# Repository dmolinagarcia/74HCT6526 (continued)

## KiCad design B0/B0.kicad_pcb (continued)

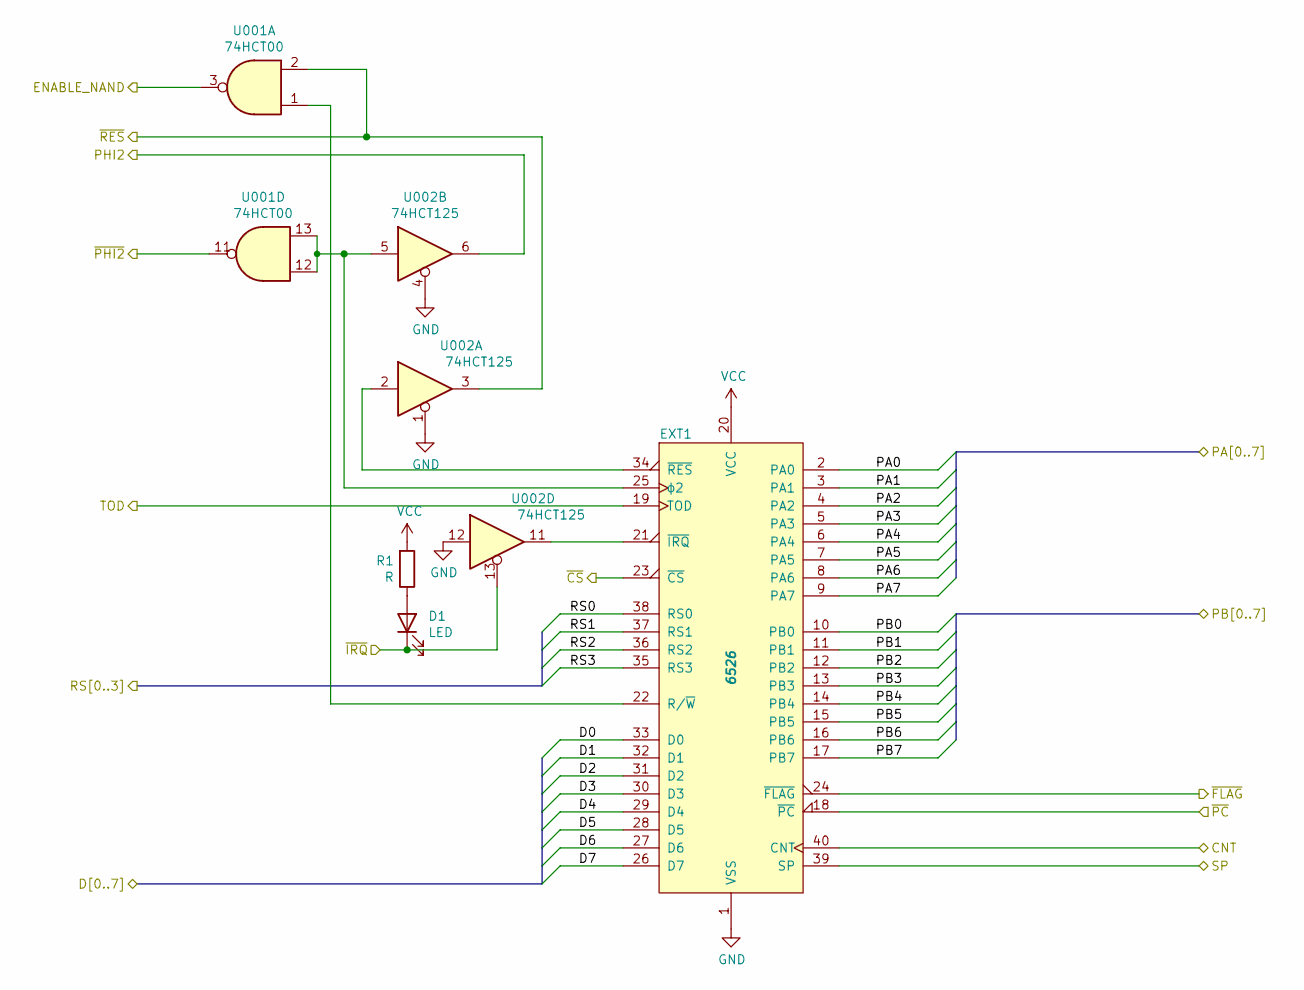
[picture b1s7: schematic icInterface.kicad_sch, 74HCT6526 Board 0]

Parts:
D1: LED; LED_0805_2012Metric
EXT1: 6526; IC Interface 2x20
R1: R; R_0805_2012Metric
U001: 74HCT00; SO-14
U002: 74HCT125; SO-14

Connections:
/icInterface/PA0: EXT1.2 (PA0); also elsewhere on the board
/icInterface/PA1: EXT1.3 (PA1); also elsewhere on the board
/icInterface/PA2: EXT1.4 (PA2); also elsewhere on the board
/icInterface/PA3: EXT1.5 (PA3); also elsewhere on the board
/icInterface/PA4: EXT1.6 (PA4); also elsewhere on the board
/icInterface/PA5: EXT1.7 (PA5); also elsewhere on the board
/icInterface/PA6: EXT1.8 (PA6); also elsewhere on the board
/icInterface/PA7: EXT1.9 (PA7); also elsewhere on the board
/icInterface/PB0: EXT1.10 (PB0); also elsewhere on the board
/icInterface/PB1: EXT1.11 (PB1); also elsewhere on the board
/icInterface/PB2: EXT1.12 (PB2); also elsewhere on the board
/icInterface/PB3: EXT1.13 (PB3); also elsewhere on the board
/icInterface/PB4: EXT1.14 (PB4); also elsewhere on the board
/icInterface/PB5: EXT1.15 (PB5); also elsewhere on the board
/icInterface/PB6: EXT1.16 (PB6); also elsewhere on the board
/icInterface/PB7: EXT1.17 (PB7); also elsewhere on the board
/icInterface/RS0: EXT1.38 (RS0); also elsewhere on the board
/icInterface/RS1: EXT1.37 (RS1); also elsewhere on the board
/icInterface/RS2: EXT1.36 (RS2); also elsewhere on the board
/icInterface/RS3: EXT1.35 (RS3); also elsewhere on the board
/icInterface/~CS: EXT1.23 (~CS); also elsewhere on the board
/icInterface/~PC: EXT1.18 (~PC); also elsewhere on the board
/~PHI2: U001.11; also elsewhere on the board
CNT: EXT1.40 (CNT); also elsewhere on the board
D0: EXT1.33 (D0); also elsewhere on the board
D1: EXT1.32 (D1); also elsewhere on the board
D2: EXT1.31 (D2); also elsewhere on the board
D3: EXT1.30 (D3); also elsewhere on the board
D4: EXT1.29 (D4); also elsewhere on the board
D5: EXT1.28 (D5); also elsewhere on the board
D6: EXT1.27 (D6); also elsewhere on the board
D7: EXT1.26 (D7); also elsewhere on the board
ENABLE_NAND: U001.3; also elsewhere on the board
GND: EXT1.1 (VSS), U002.1, U002.4, U002.12; also elsewhere on the board
unnamed: D1.2 (A), R1.1
unnamed: EXT1.21 (~IRQ), U002.11
unnamed: EXT1.22 (R/~W), U001.1
unnamed: EXT1.25 (ϕ2), U001.12, U001.13, U002.5
unnamed: EXT1.34 (~RES), U002.2
PHI2: U002.6; also elsewhere on the board
SP: EXT1.39 (SP); also elsewhere on the board
TOD: EXT1.19 (TOD); also elsewhere on the board
VCC: EXT1.20 (VCC), R1.2; also elsewhere on the board
~FLAG: EXT1.24 (~FLAG); also elsewhere on the board
~IRQ: D1.1 (K), U002.13; also elsewhere on the board
~RES: U001.2, U002.3; also elsewhere on the board

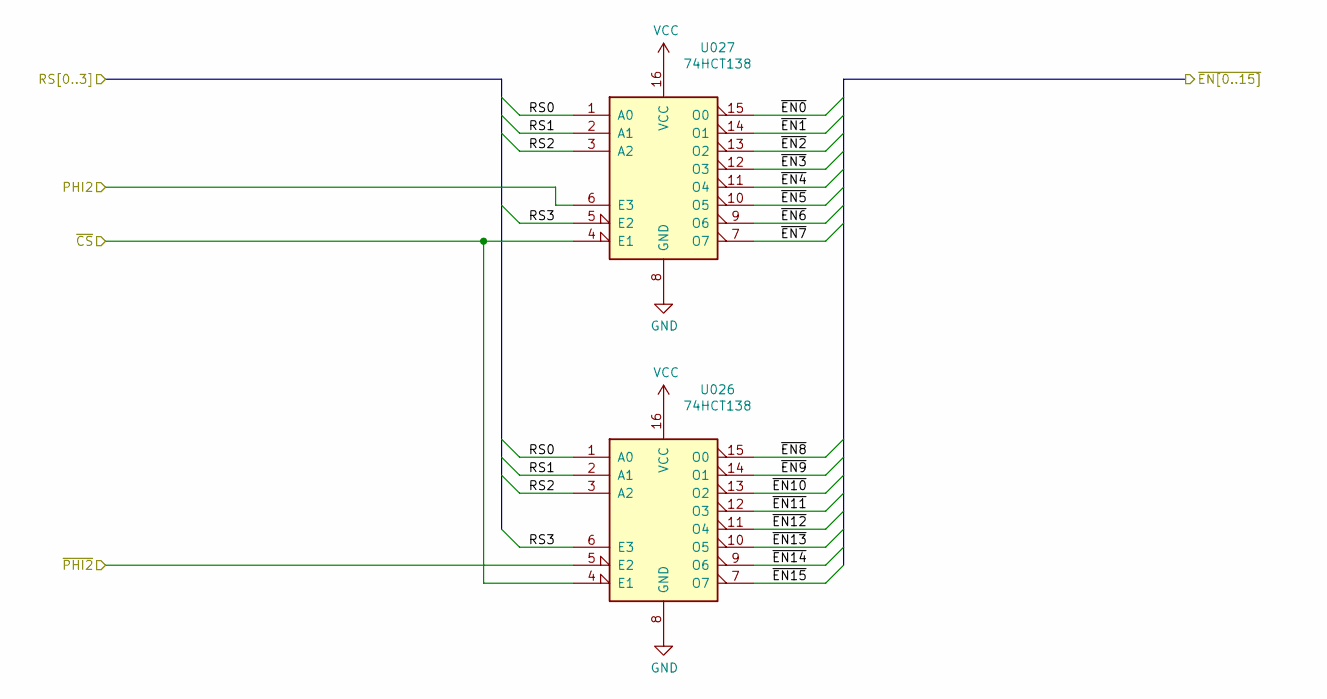
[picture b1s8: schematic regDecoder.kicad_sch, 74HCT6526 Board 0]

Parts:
U026, U027: 74HCT138; SO-16

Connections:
/icInterface/RS0: U026.1 (A0), U027.1 (A0); also elsewhere on the board
/icInterface/RS1: U026.2 (A1), U027.2 (A1); also elsewhere on the board
/icInterface/RS2: U026.3 (A2), U027.3 (A2); also elsewhere on the board
/icInterface/RS3: U026.6 (E3), U027.5 (E2); also elsewhere on the board
/icInterface/~CS: U026.4 (E1), U027.4 (E1); also elsewhere on the board
/~PHI2: U026.5 (E2); also elsewhere on the board
GND: U026.8 (GND), U027.8 (GND); also elsewhere on the board
PHI2: U027.6 (E3); also elsewhere on the board
VCC: U026.16 (VCC), U027.16 (VCC); also elsewhere on the board
~EN0: U027.15 (O0); also elsewhere on the board
~EN1: U027.14 (O1); also elsewhere on the board
~EN2: U027.13 (O2); also elsewhere on the board
~EN3: U027.12 (O3); also elsewhere on the board
~EN4: U027.11 (O4); also elsewhere on the board
~EN5: U027.10 (O5); also elsewhere on the board
~EN6: U027.9 (O6); also elsewhere on the board
~EN7: U027.7 (O7); also elsewhere on the board
~EN8: U026.15 (O0); also elsewhere on the board
~EN9: U026.14 (O1); also elsewhere on the board
~EN10: U026.13 (O2); also elsewhere on the board
~EN11: U026.12 (O3); also elsewhere on the board
~EN12: U026.11 (O4); also elsewhere on the board
~EN13: U026.10 (O5); also elsewhere on the board
~EN14: U026.9 (O6); also elsewhere on the board
~EN15: U026.7 (O7); also elsewhere on the board

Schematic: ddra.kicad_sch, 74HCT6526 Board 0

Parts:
U003: 74HC244; SOIC-20W
U007: 74HC32; SO-14
U023: 74HC377; SOIC-20W
U028, U029: 74HC00; SO-14

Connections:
/ddra/DDRA0: U003.8 (1A3), U023.2 (Q0); also elsewhere on the board
/ddra/DDRA1: U003.11 (2A3), U023.5 (Q1); also elsewhere on the board
/ddra/DDRA2: U003.6 (1A2), U023.6 (Q2); also elsewhere on the board
/ddra/DDRA3: U003.13 (2A2), U023.9 (Q3); also elsewhere on the board
/ddra/DDRA4: U003.4 (1A1), U023.12 (Q4); also elsewhere on the board
/ddra/DDRA5: U003.15 (2A1), U023.15 (Q5); also elsewhere on the board
/ddra/DDRA6: U003.2 (1A0), U023.16 (Q6); also elsewhere on the board
/ddra/DDRA7: U003.17 (2A0), U023.19 (Q7); also elsewhere on the board
/ddra/~OE2: U003.1 (1OE), U003.19 (2OE), U007.11
/ddra/~WE2: U023.1 (~E), U029.6
/~PHI2: U023.11 (CP); also elsewhere on the board
D0: U003.12 (1Y3); also elsewhere on the board
D1: U003.9 (2Y3); also elsewhere on the board
D2: U003.14 (1Y2); also elsewhere on the board
D3: U003.7 (2Y2); also elsewhere on the board
D4: U003.16 (1Y1); also elsewhere on the board
D5: U003.5 (2Y1); also elsewhere on the board
D6: U003.18 (1Y0); also elsewhere on the board
D7: U003.3 (2Y0); also elsewhere on the board
DZ0: U023.3 (D0); also elsewhere on the board
DZ1: U023.4 (D1); also elsewhere on the board
DZ2: U023.7 (D2); also elsewhere on the board
DZ3: U023.8 (D3); also elsewhere on the board
DZ4: U023.13 (D4); also elsewhere on the board
DZ5: U023.14 (D5); also elsewhere on the board
DZ6: U023.17 (D6); also elsewhere on the board
DZ7: U023.18 (D7); also elsewhere on the board
ENABLE_NAND: U007.12, U029.4; also elsewhere on the board
GND: U003.10 (GND), U023.10 (GND); also elsewhere on the board
unnamed: U028.8, U029.5
VCC: U003.20 (VCC), U023.20 (VCC); also elsewhere on the board
~EN2: U007.13, U028.10; also elsewhere on the board
~RES: U028.9; also elsewhere on the board

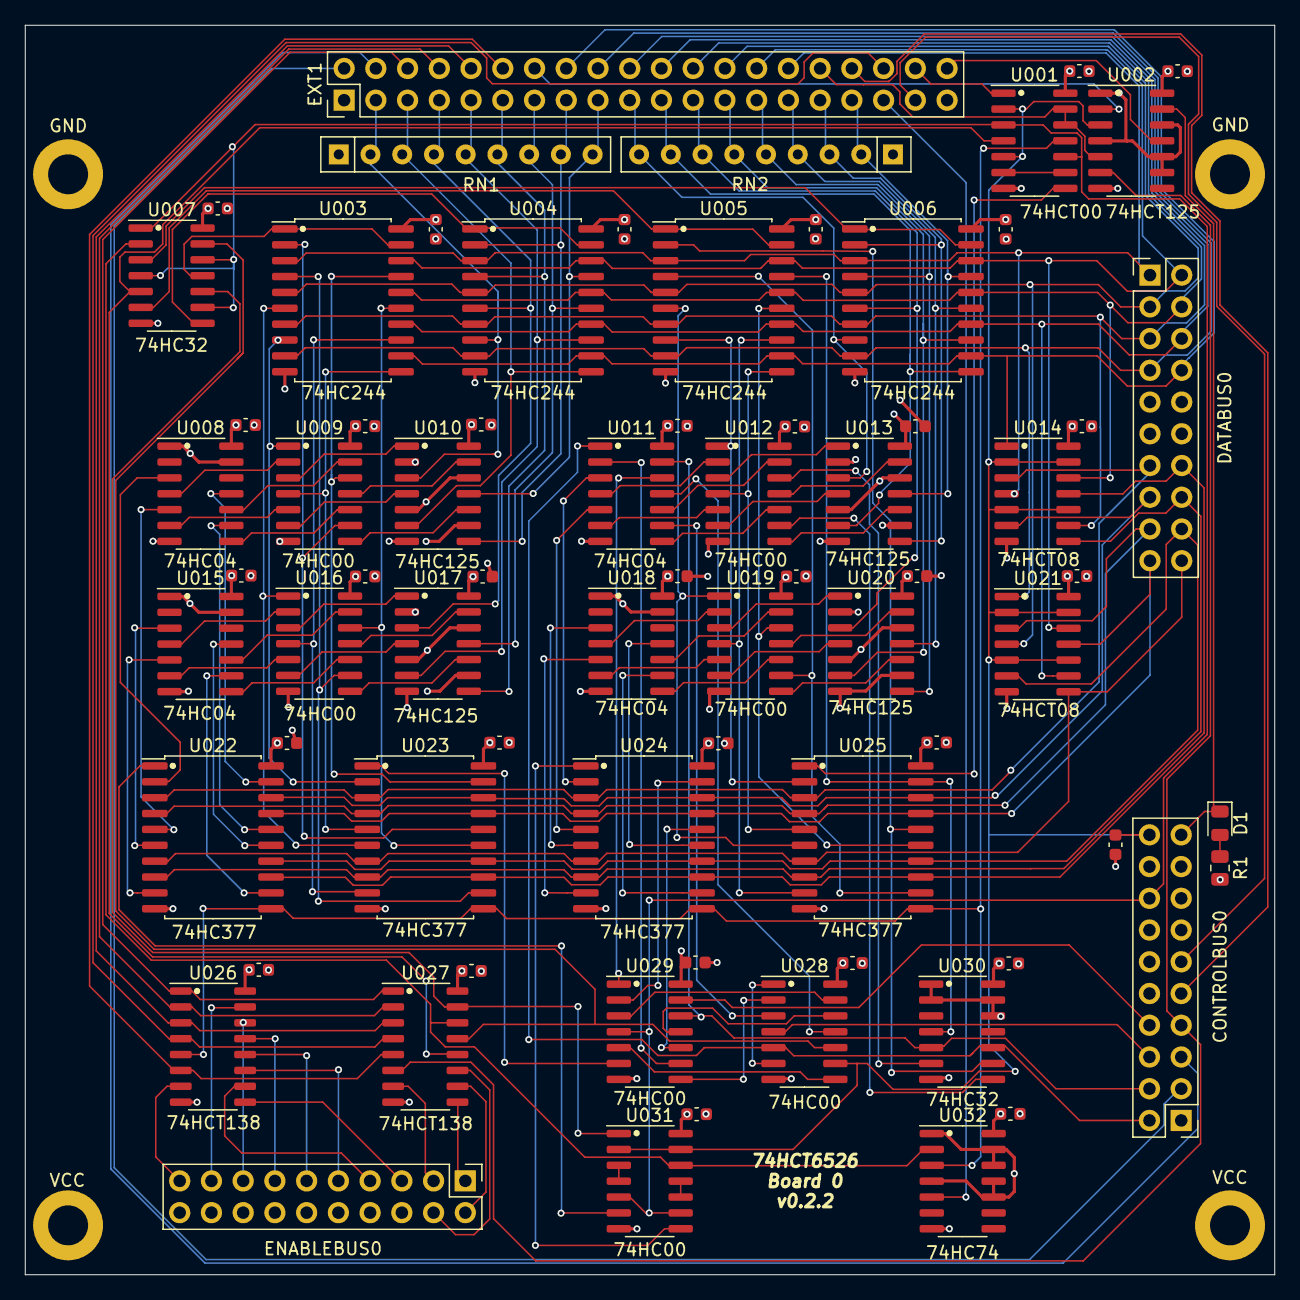
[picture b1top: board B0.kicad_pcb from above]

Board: 4 copper layers, 100.0 x 100.0 mm, 77 parts (0 on the bottom side), 160 nets.

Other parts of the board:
GND1, GND2: GND; MountingHole_2.2mm_M2_DIN965_Pad
VCC1, VCC2: VCC; MountingHole_2.2mm_M2_DIN965_Pad

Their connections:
GND: GND1.GND, GND2.GND; also elsewhere on the board
VCC: VCC1.VCC, VCC2.VCC2; also elsewhere on the board

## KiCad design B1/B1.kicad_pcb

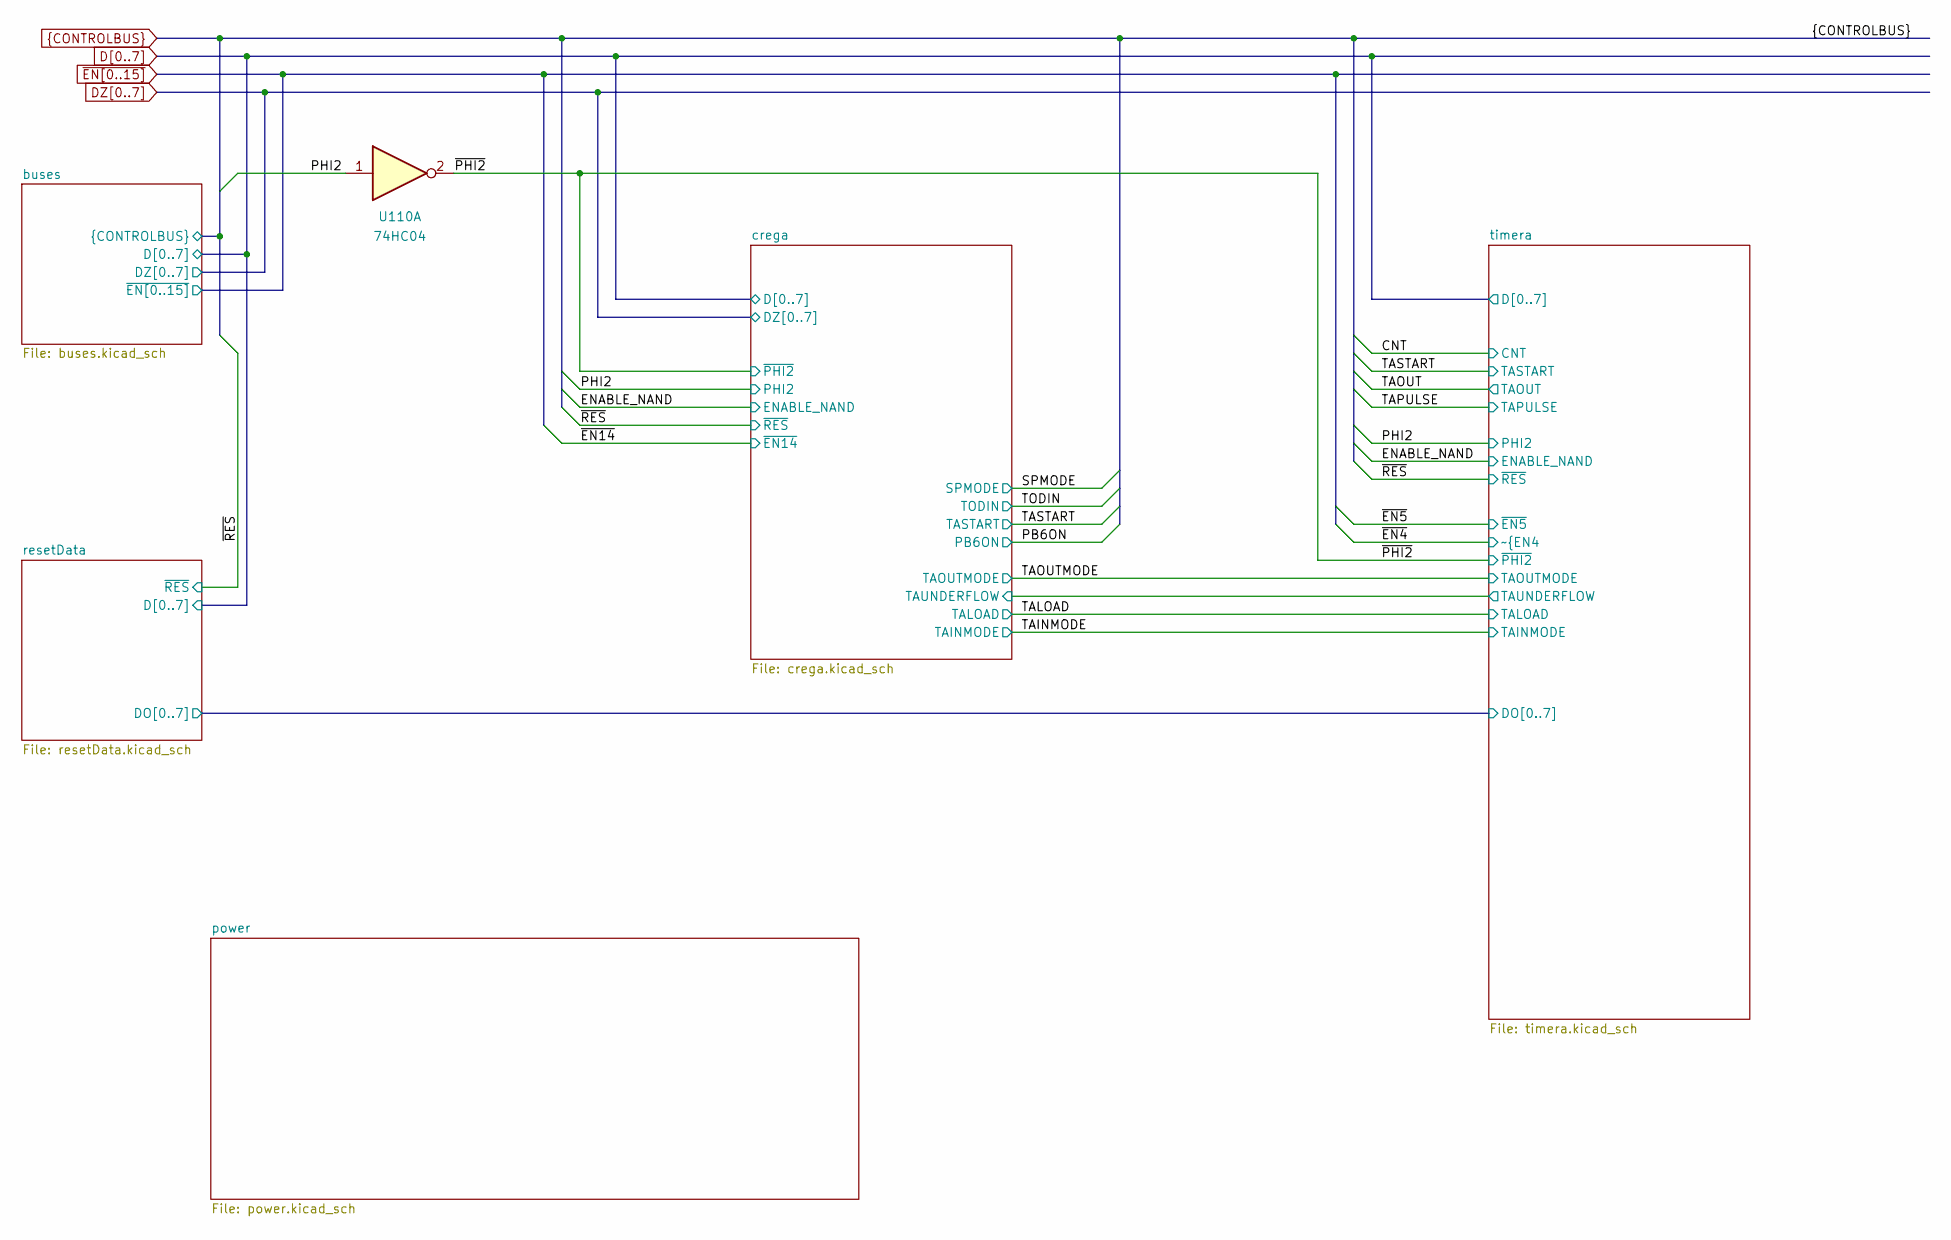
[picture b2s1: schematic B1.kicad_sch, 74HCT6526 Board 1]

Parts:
U110: 74HC04; SOIC-14_3.9x8.7mm_P1.27mm

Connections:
/~PHI2: U110.2; also elsewhere on the board
PHI2: U110.1; also elsewhere on the board

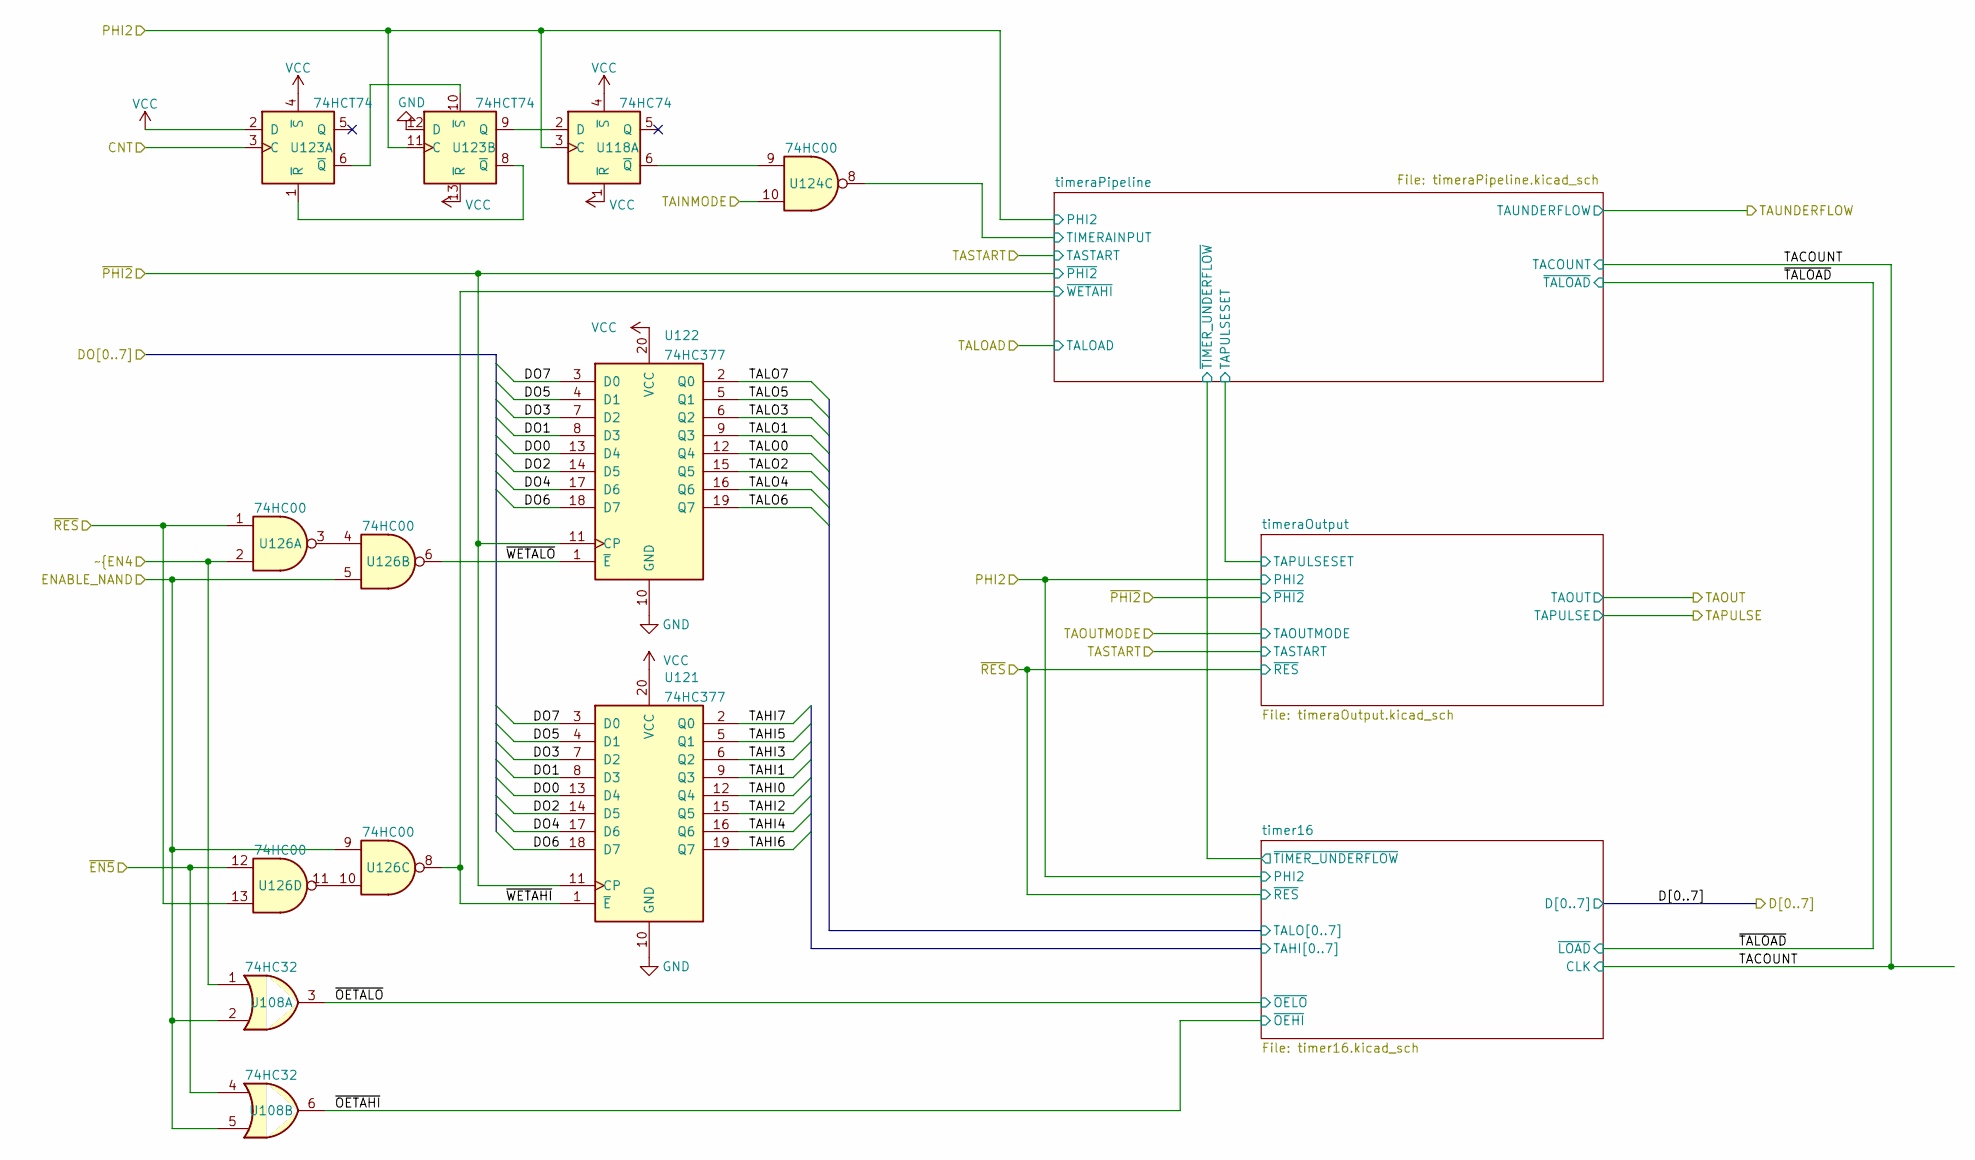
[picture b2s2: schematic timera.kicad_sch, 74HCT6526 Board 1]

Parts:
U108: 74HC32; SOIC-14_3.9x8.7mm_P1.27mm
U118: 74HC74; SO-14_3.9x8.65mm_P1.27mm
U121, U122: 74HC377; SOIC-20W_7.5x12.8mm_P1.27mm
U123: 74HCT74; SO-14_3.9x8.65mm_P1.27mm
U124: 74HC00; SOIC-14_3.9x8.7mm_P1.27mm
U126: 74HC00; SO-14_3.9x8.65mm_P1.27mm

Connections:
/TAINMODE: U124.10; also elsewhere on the board
/resetData/DO0: U121.13 (D4), U122.13 (D4); also elsewhere on the board
/resetData/DO1: U121.8 (D3), U122.8 (D3); also elsewhere on the board
/resetData/DO2: U121.14 (D5), U122.14 (D5); also elsewhere on the board
/resetData/DO3: U121.7 (D2), U122.7 (D2); also elsewhere on the board
/resetData/DO4: U121.17 (D6), U122.17 (D6); also elsewhere on the board
/resetData/DO5: U121.4 (D1), U122.4 (D1); also elsewhere on the board
/resetData/DO6: U121.18 (D7), U122.18 (D7); also elsewhere on the board
/resetData/DO7: U121.3 (D0), U122.3 (D0); also elsewhere on the board
/timera/timer16/TAHI0: U121.12 (Q4); also elsewhere on the board
/timera/timer16/TAHI1: U121.9 (Q3); also elsewhere on the board
/timera/timer16/TAHI2: U121.15 (Q5); also elsewhere on the board
/timera/timer16/TAHI3: U121.6 (Q2); also elsewhere on the board
/timera/timer16/TAHI4: U121.16 (Q6); also elsewhere on the board
/timera/timer16/TAHI5: U121.5 (Q1); also elsewhere on the board
/timera/timer16/TAHI6: U121.19 (Q7); also elsewhere on the board
/timera/timer16/TAHI7: U121.2 (Q0); also elsewhere on the board
/timera/timer16/TALO0: U122.12 (Q4); also elsewhere on the board
/timera/timer16/TALO1: U122.9 (Q3); also elsewhere on the board
/timera/timer16/TALO2: U122.15 (Q5); also elsewhere on the board
/timera/timer16/TALO3: U122.6 (Q2); also elsewhere on the board
/timera/timer16/TALO4: U122.16 (Q6); also elsewhere on the board
/timera/timer16/TALO5: U122.5 (Q1); also elsewhere on the board
/timera/timer16/TALO6: U122.19 (Q7); also elsewhere on the board
/timera/timer16/TALO7: U122.2 (Q0); also elsewhere on the board
/timera/timeraPipeline/TIMERAINPUT: U124.8; also elsewhere on the board
/timera/~OETAHI: U108.6; also elsewhere on the board
/timera/~OETALO: U108.3; also elsewhere on the board
/timera/~WETAHI: U121.1 (~E), U126.8; also elsewhere on the board
/timera/~WETALO: U122.1 (~E), U126.6
/~PHI2: U121.11 (CP), U122.11 (CP); also elsewhere on the board
CNT: U123.3 (C); also elsewhere on the board
ENABLE_NAND: U108.2, U108.5, U126.5, U126.9; also elsewhere on the board
GND: U121.10 (GND), U122.10 (GND), U123.12 (D); also elsewhere on the board
unnamed: U118.2 (D), U123.9 (Q)
unnamed: U118.6 (~Q), U124.9
unnamed: U123.1 (~R), U123.8 (~Q)
unnamed: U123.6 (~Q), U123.10 (~S)
unnamed: U126.3, U126.4
unnamed: U126.10, U126.11
PHI2: U118.3 (C), U123.11 (C); also elsewhere on the board
VCC: U118.1 (~R), U118.4 (~S), U121.20 (VCC), U122.20 (VCC), U123.2 (D), U123.4 (~S), U123.13 (~R); also elsewhere on the board
~EN4: U108.1, U126.2; also elsewhere on the board
~EN5: U108.4, U126.12; also elsewhere on the board
~RES: U126.1, U126.13; also elsewhere on the board

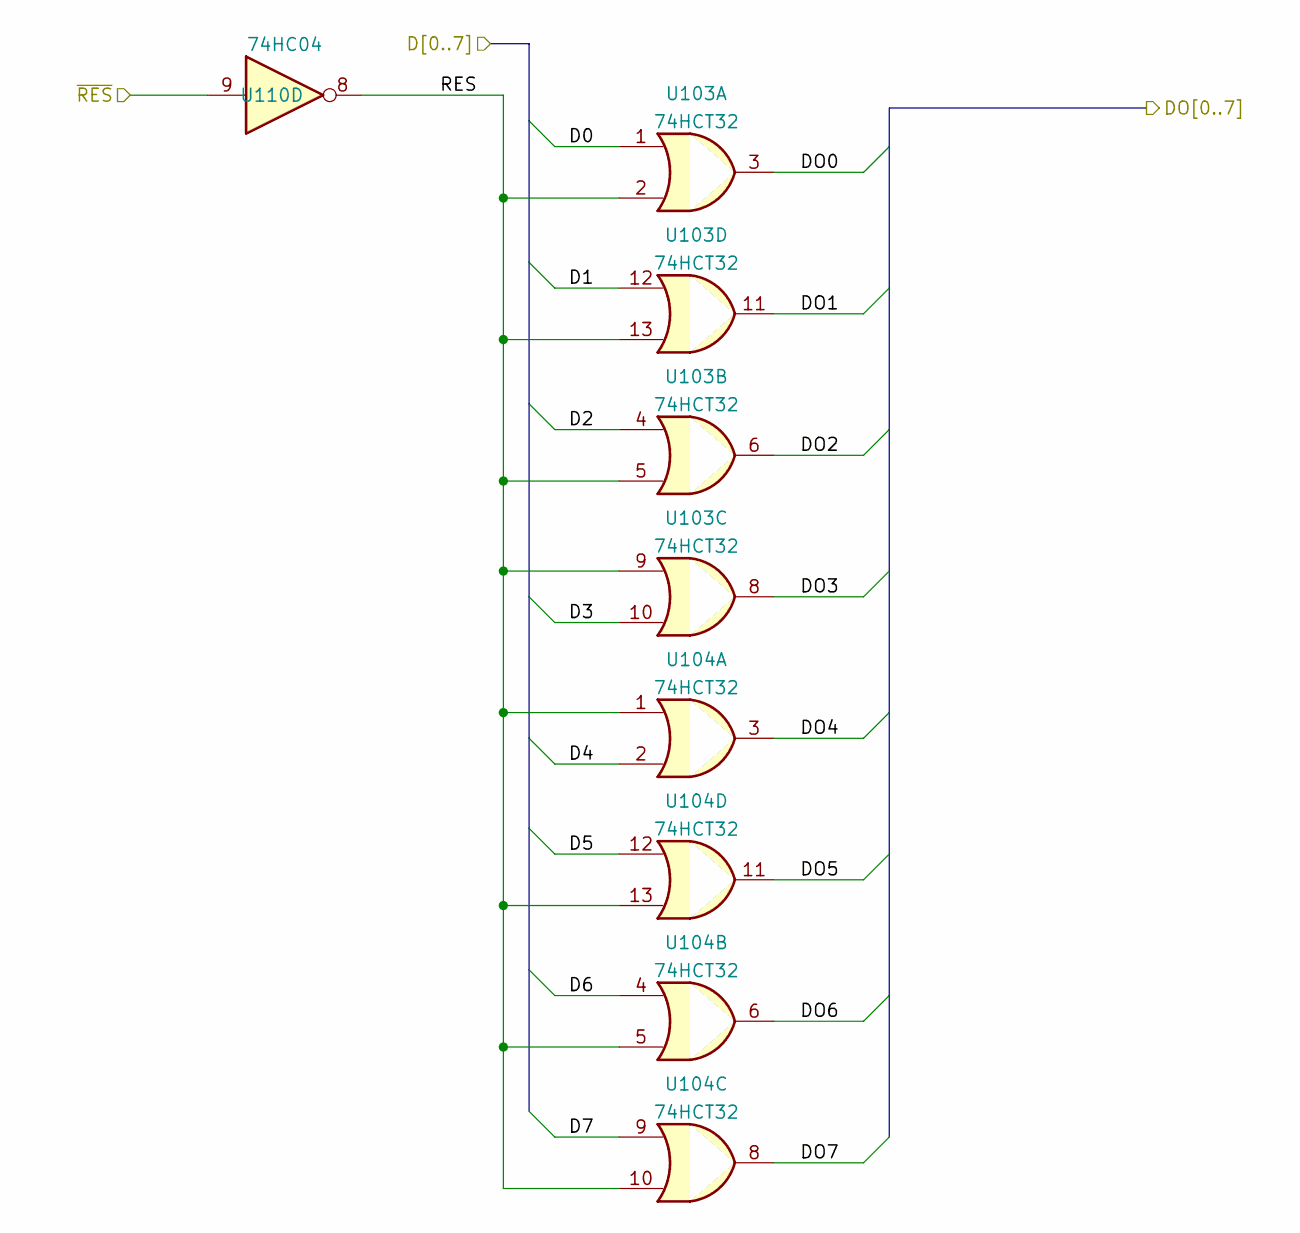
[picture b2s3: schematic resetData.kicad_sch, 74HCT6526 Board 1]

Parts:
U103, U104: 74HCT32; SO-14_3.9x8.65mm_P1.27mm
U110: 74HC04; SOIC-14_3.9x8.7mm_P1.27mm

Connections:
/resetData/DO0: U103.3; also elsewhere on the board
/resetData/DO1: U103.11; also elsewhere on the board
/resetData/DO2: U103.6; also elsewhere on the board
/resetData/DO3: U103.8; also elsewhere on the board
/resetData/DO4: U104.3; also elsewhere on the board
/resetData/DO5: U104.11; also elsewhere on the board
/resetData/DO6: U104.6; also elsewhere on the board
/resetData/DO7: U104.8; also elsewhere on the board
/resetData/RES: U103.2, U103.5, U103.9, U103.13, U104.1, U104.5, U104.10, U104.13, U110.8
D0: U103.1; also elsewhere on the board
D1: U103.12; also elsewhere on the board
D2: U103.4; also elsewhere on the board
D3: U103.10; also elsewhere on the board
D4: U104.2; also elsewhere on the board
D5: U104.12; also elsewhere on the board
D6: U104.4; also elsewhere on the board
D7: U104.9; also elsewhere on the board
~RES: U110.9; also elsewhere on the board

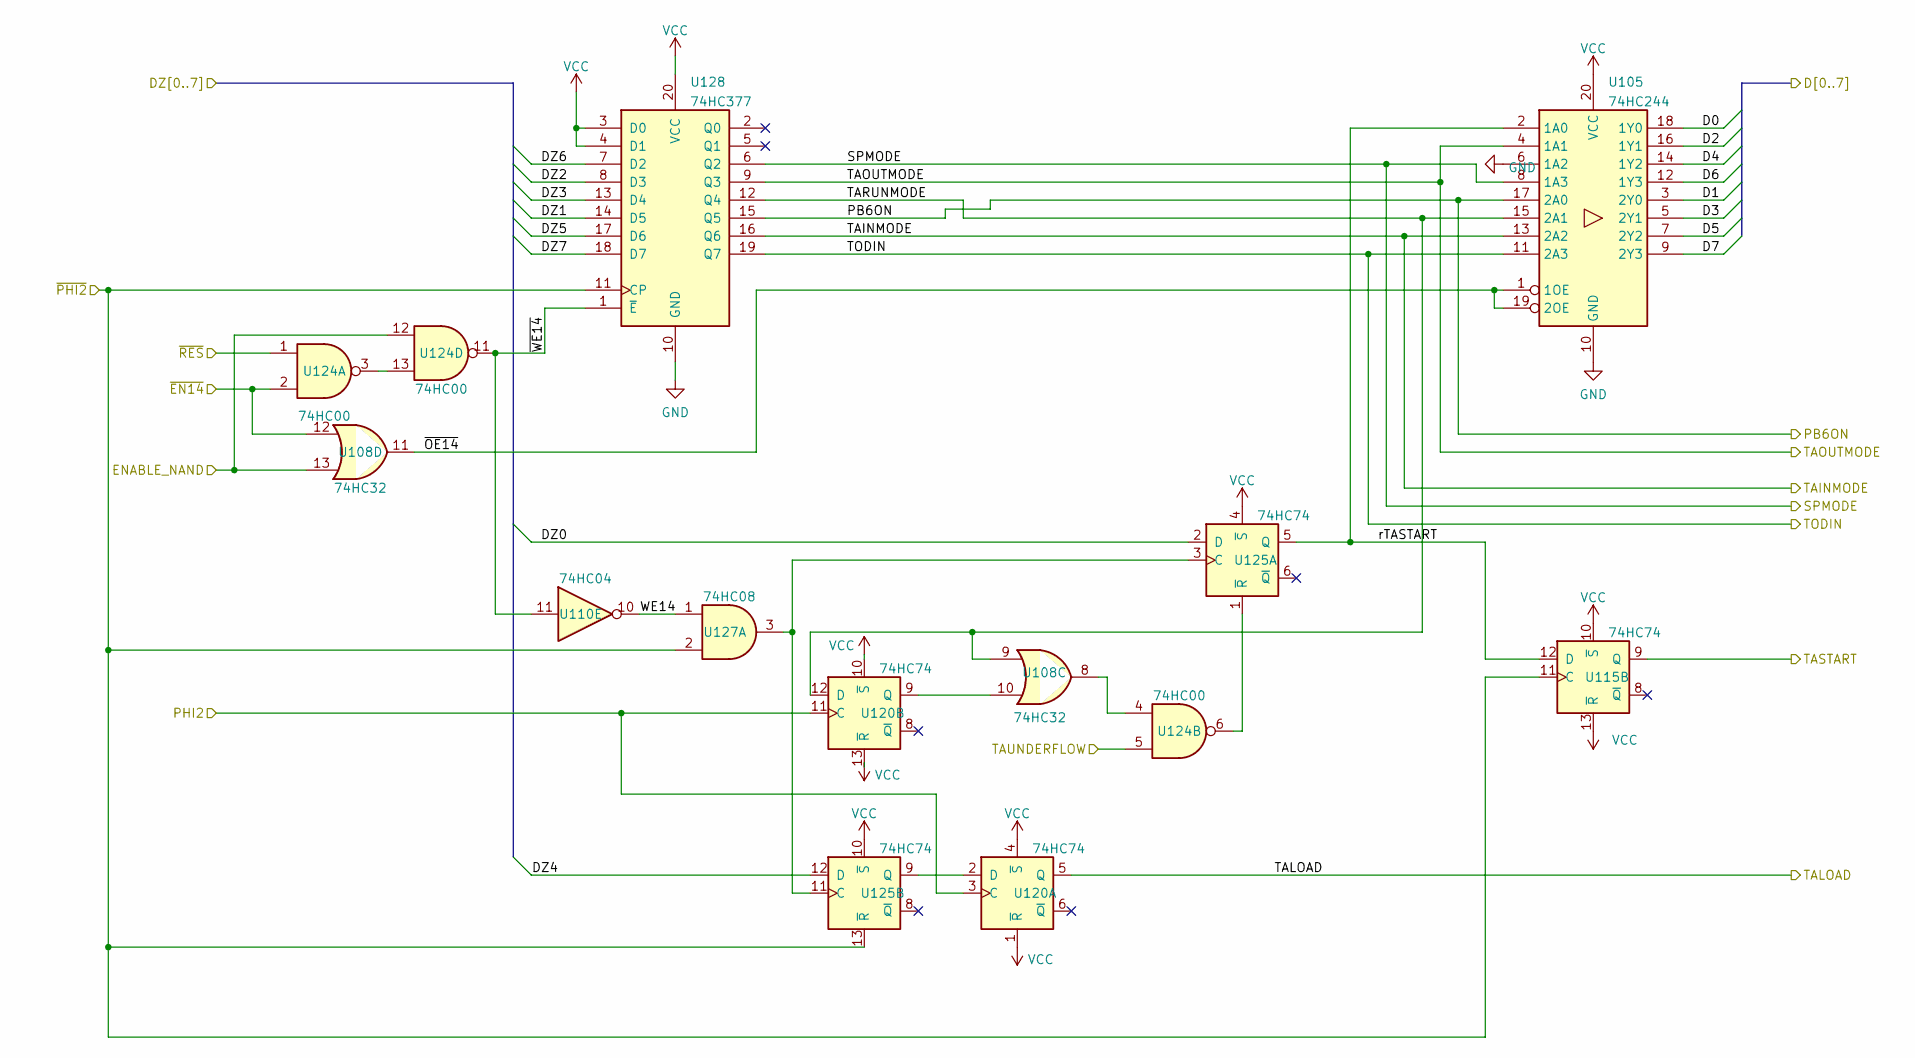
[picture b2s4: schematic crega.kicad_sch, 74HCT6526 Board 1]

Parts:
U105: 74HC244; SOIC-20W_7.5x12.8mm_P1.27mm
U108: 74HC32; SOIC-14_3.9x8.7mm_P1.27mm
U110: 74HC04; SOIC-14_3.9x8.7mm_P1.27mm
U115, U120, U125: 74HC74; SO-14_3.9x8.65mm_P1.27mm
U124: 74HC00; SOIC-14_3.9x8.7mm_P1.27mm
U127: 74HC08; SO-14_3.9x8.65mm_P1.27mm
U128: 74HC377; SOIC-20W_7.5x12.8mm_P1.27mm

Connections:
/TAINMODE: U105.13 (2A2), U128.16 (Q6); also elsewhere on the board
/TALOAD: U120.5 (Q); also elsewhere on the board
/TAOUTMODE: U105.4 (1A1), U128.9 (Q3); also elsewhere on the board
/crega/TARUNMODE: U105.15 (2A1), U108.9, U120.12 (D), U128.12 (Q4)
/crega/TAUNDERFLOW: U124.5; also elsewhere on the board
/crega/WE14: U110.10, U127.1
/crega/rTASTART: U105.2 (1A0), U115.12 (D), U125.5 (Q)
/crega/~OE14: U105.1 (1OE), U105.19 (2OE), U108.11
/crega/~WE14: U110.11, U124.11, U128.1 (~E)
/~PHI2: U115.11 (C), U125.13 (~R), U127.2, U128.11 (CP); also elsewhere on the board
D0: U105.18 (1Y0); also elsewhere on the board
D1: U105.3 (2Y0); also elsewhere on the board
D2: U105.16 (1Y1); also elsewhere on the board
D3: U105.5 (2Y1); also elsewhere on the board
D4: U105.14 (1Y2); also elsewhere on the board
D5: U105.7 (2Y2); also elsewhere on the board
D6: U105.12 (1Y3); also elsewhere on the board
D7: U105.9 (2Y3); also elsewhere on the board
DZ0: U125.2 (D); also elsewhere on the board
DZ1: U128.14 (D5); also elsewhere on the board
DZ2: U128.8 (D3); also elsewhere on the board
DZ3: U128.13 (D4); also elsewhere on the board
DZ4: U125.12 (D); also elsewhere on the board
DZ5: U128.17 (D6); also elsewhere on the board
DZ6: U128.7 (D2); also elsewhere on the board
DZ7: U128.18 (D7); also elsewhere on the board
ENABLE_NAND: U108.13, U124.12; also elsewhere on the board
GND: U105.6 (1A2), U105.10 (GND), U128.10 (GND); also elsewhere on the board
unnamed: U108.8, U124.4
unnamed: U108.10, U120.9 (Q)
unnamed: U120.2 (D), U125.9 (Q)
unnamed: U124.6, U125.1 (~R)
unnamed: U124.3, U124.13
unnamed: U125.3 (C), U125.11 (C), U127.3
PB6ON: U105.17 (2A0), U128.15 (Q5); also elsewhere on the board
PHI2: U120.3 (C), U120.11 (C); also elsewhere on the board
SPMODE: U105.8 (1A3), U128.6 (Q2); also elsewhere on the board
TASTART: U115.9 (Q); also elsewhere on the board
TODIN: U105.11 (2A3), U128.19 (Q7); also elsewhere on the board
VCC: U105.20 (VCC), U115.10 (~S), U115.13 (~R), U120.1 (~R), U120.4 (~S), U120.10 (~S), U120.13 (~R), U125.4 (~S), U125.10 (~S), U128.3 (D0), U128.4 (D1), U128.20 (VCC); also elsewhere on the board
~EN14: U108.12, U124.2; also elsewhere on the board
~RES: U124.1; also elsewhere on the board

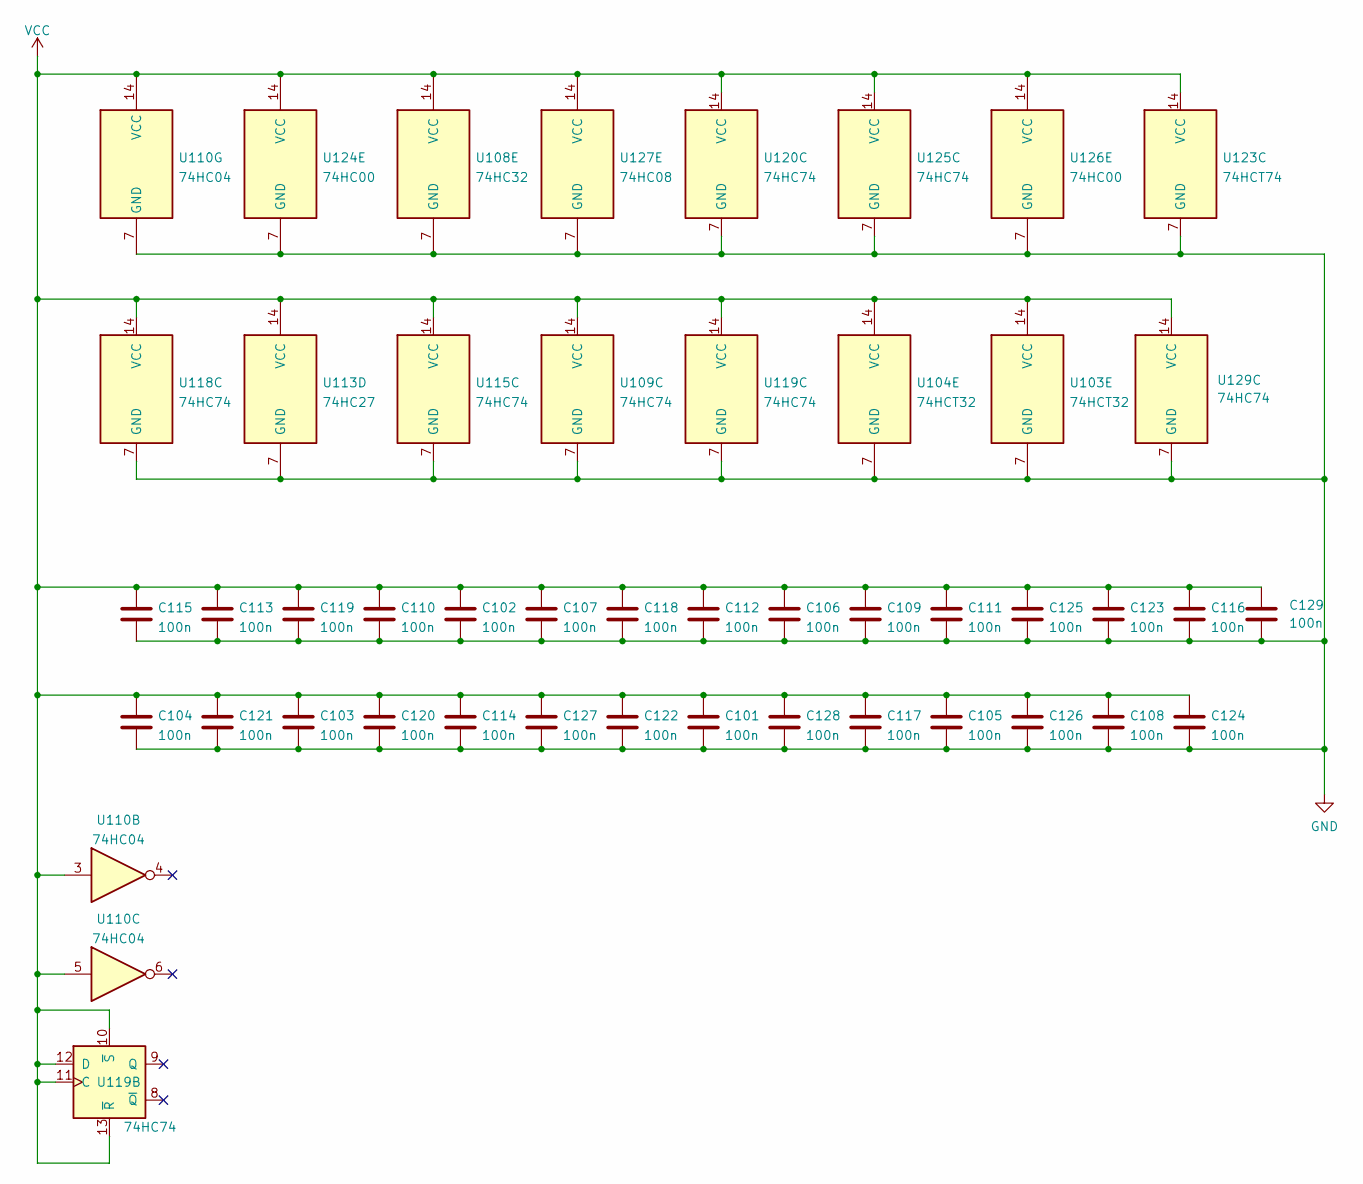
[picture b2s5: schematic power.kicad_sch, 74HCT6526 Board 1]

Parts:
C101, C102, C103, C104, C105, C106, C107, C108, C109, C110, C111, C112, C113, C114, C115, C116, C117, C118, C119, C120, C121, C122, C123, C124, C125, C126, C127, C128, C129: 100n; C_0603_1608Metric
U103, U104: 74HCT32; SO-14_3.9x8.65mm_P1.27mm
U108: 74HC32; SOIC-14_3.9x8.7mm_P1.27mm
U109, U115, U118, U119, U120, U125, U129: 74HC74; SO-14_3.9x8.65mm_P1.27mm
U110: 74HC04; SOIC-14_3.9x8.7mm_P1.27mm
U113: 74HC27; SO-14_3.9x8.65mm_P1.27mm
U123: 74HCT74; SO-14_3.9x8.65mm_P1.27mm
U124: 74HC00; SOIC-14_3.9x8.7mm_P1.27mm
U126: 74HC00; SO-14_3.9x8.65mm_P1.27mm
U127: 74HC08; SO-14_3.9x8.65mm_P1.27mm

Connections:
GND: C101.2, C102.2, C103.2, C104.2, C105.2, C106.2, C107.2, C108.2, C109.2, C110.2, C111.2, C112.2, C113.2, C114.2, C115.2, C116.2, C117.2, C118.2, C119.2, C120.2, C121.2, C122.2, C123.2, C124.2, C125.2, C126.2, C127.2, C128.2, C129.2, U103.7 (GND), U104.7 (GND), U108.7 (GND), U109.7 (GND), U110.7 (GND), U113.7 (GND), U115.7 (GND), U118.7 (GND), U119.7 (GND), U120.7 (GND), U123.7 (GND), U124.7 (GND), U125.7 (GND), U126.7 (GND), U127.7 (GND), U129.7 (GND); also elsewhere on the board
VCC: C101.1, C102.1, C103.1, C104.1, C105.1, C106.1, C107.1, C108.1, C109.1, C110.1, C111.1, C112.1, C113.1, C114.1, C115.1, C116.1, C117.1, C118.1, C119.1, C120.1, C121.1, C122.1, C123.1, C124.1, C125.1, C126.1, C127.1, C128.1, C129.1, U103.14 (VCC), U104.14 (VCC), U108.14 (VCC), U109.14 (VCC), U110.3, U110.5, U110.14 (VCC), U113.14 (VCC), U115.14 (VCC), U118.14 (VCC), U119.10 (~S), U119.11 (C), U119.12 (D), U119.13 (~R), U119.14 (VCC), U120.14 (VCC), U123.14 (VCC), U124.14 (VCC), U125.14 (VCC), U126.14 (VCC), U127.14 (VCC), U129.14 (VCC); also elsewhere on the board
